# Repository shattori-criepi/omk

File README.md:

# OMK — おうちモニタキット

おうちモニタキット（OMK）は、一般財団法人電力中央研究所が開発した、住宅内の電力・環境・行動を計測するオープンなIoT基盤です。計測したい項目に合わせてセンサを組み合わせ、Raspberry Piをデータ収集・保存の中心となるGatewayとして使います。標準構成では、構築後は住宅側ネットワークに依存せず運用できます。

## できること

- 対応するセンサ・機器から、住宅の温度、湿度、空気質、電力、在不在などのデータを計測・収集できます。
- Raspberry Piに計測データを保存し、長期間の履歴として蓄積できます。
- Gateway内のローカルDashboardで、現在の計測値と機器の状態を確認できます。
- 保存済みデータをCSV/ZIPとしてUSBメモリへ書き出せます。
- SORACOM Harvestを利用する場合は、計測データをクラウドへ送信して保管できます。

## OMKの製作方法

初めて製作する方は、以下を上から順に読み、各ページ末尾の「次へ」で進めてください。GatewayとSEN66 Nodeを製作し、4-1のDashboardで計測確認まで完了します。

### 1. OMKの概要

- [1-1. OMK導入ガイド](docs/user/getting-started.md)
- [1-2. 対応センサ・機器と取得データ](docs/user/supported-devices.md)

### 2. OMK Gatewayを製作・セットアップする

- [2-1. OMKのパーツ構成](docs/user/parts-list.md)
- [2-2. Gatewayの組み立て](docs/user/gateway-assembly.md)
- [2-3. Gatewayセットアップ](docs/user/gateway-setup.md)

### 3. SEN66 Nodeを製作・セットアップする

- [3-1. SEN66 Nodeの組み立て](docs/user/sen66-node-assembly.md)
- [3-2. SEN66 Nodeをセットアップする](docs/user/esp32-node-setup.md)

### 4. Dashboardを使う

- [4-1. Dashboardの使い方](docs/user/dashboard.md)

ここまでで、推奨構成のOMKの製作・セットアップとSEN66による計測確認は完了です。

## 必要に応じて行う作業

製作完了後に、目的に合うページを選んでください。

- [BLEセンサを追加する](docs/user/ble-sensor-setup.md)
- [Bルートでスマートメーターを追加する](docs/user/broute-setup.md)
- [OMK Nodeで計測範囲を拡張する](docs/user/node-and-sensors.md)
- [中継専用OMK Nodeをセットアップする](docs/user/relay-node-setup.md)
- [Gatewayソフトウェアを更新・保守する](docs/user/gateway-maintenance.md)
- [OMK Nodeを更新・再設定する](docs/user/node-maintenance.md)
- [標準構成以外・高度な構成](docs/user/advanced-configuration.md)

## 参考情報

- [用語集](docs/user/glossary.md)
- [トラブルシューティング](docs/user/troubleshooting.md)

## 対応機器と取得データ

主な対応機器と取得データは次のとおりです。計測項目、接続方式、対応範囲の詳細は[「1-2. 対応センサ・機器と取得データ」](docs/user/supported-devices.md)を参照してください。

| 機器・センサ | 主な取得データ |
| --- | --- |
| 低圧スマートメーター（Bルート） | 系統の瞬時電力、買電・売電の積算電力量、30分ごとの買電量・売電量 |
| Sensirion SEN66 | 温度、相対湿度、CO₂濃度、粒子状物質、VOC Index、NOx Index |
| SwitchBot BLEセンサ | 温湿度、CO₂濃度、人感、開閉、プラグの消費電力・スイッチ状態、防水温湿度 |

## 動作確認環境と利用上の前提

OMKで動作確認している推奨構成は次のとおりです。

- Gateway：**Raspberry Pi 4、Raspberry Pi Touch Display 2（7インチ）、SORACOM Onyx**。OSは64ビットのRaspberry Pi OSを使用します。
- SEN66 Node：Sensirion SEN66とAtomS3 Lite。

初期セットアップには、既存Wi-Fiなどのインターネット接続を使います。APはAccess Point（アクセスポイント）の略です。OMK APを有効にすると、Raspberry Piの内蔵Wi-FiはOMK AP専用となり、外部Wi-Fiには接続できません。推奨構成ではSORACOM Onyxを外部通信と遠隔管理に使います。

標準構成以外の対応範囲と制約は、[「標準構成以外・高度な構成」](docs/user/advanced-configuration.md)を参照してください。

## OMKを開発する

このブランチは実機未検証のNative Mesh P1試験版です。[固定成果物・再現手順](experiments/native-mesh-p1-20261110/README.txt)と[移行資料](docs/developer/native-mesh-migration.md)を参照してください。既存公開用prebuiltは旧方式であり、今回の試験には使用しません。

- [アーキテクチャ](docs/developer/architecture.md)
- [開発ガイド](docs/developer/development.md)
- [Gatewayネットワーク設計](docs/developer/networking.md)
- [データ経路とMQTT仕様](docs/developer/data-and-mqtt.md)
- [リポジトリ構成](docs/developer/repository-structure.md)
- [設計判断の記録](docs/decisions/)

各サービスとファームウェアのREADMEには、個別の起動・設定・テスト・デバッグ方法を記載しています。

## 利用上の注意

OMKは研究・実験用途のシステムであり、商用製品やサービスではありません。計測値の正確性、完全性、継続性、対応機器との互換性、安定動作および安全性は保証しません。利用、改変、機器への接続、再配布は各利用者の判断と責任で行ってください。料金精算、契約上の計量、安全制御、保護制御など、高い信頼性を要する用途での利用は想定していません。

無保証および責任制限は[LICENSE](LICENSE)を参照してください。

## 成果発表

OMKを使用した技術開発等の成果を発表・報告する際は、可能な範囲でOMKを使用した旨の表示をお願いします。

## サポートと開発方針

GitHub等から利用する場合、機器の準備、構築、設定、運用、保守は利用者自身で行います。研究所および開発者は、個別環境への導入・設定支援、機器の製作代行、トラブル対応などの個別サポート、保守、動作保証を提供しません。

活用例、アイデア、改善案など、OMK全体に有用な情報の共有は歓迎します。ただし、相談や要望に対する回答、調査、機能追加、機器対応、修正などの対応は約束しません。

特定の利用者だけに必要な機能は、利用者自身のforkで開発・維持することを想定します。OMK全体に有用なアイデアは、研究目的、汎用性、保守性、開発優先度などを踏まえて採用を検討します。提案者にPR作成を求めるとは限らず、OMK開発側が実装する場合や、実装を見送る場合もあります。

GitHubでの情報共有・提案は、次の方針で受け付けます。

- GitHub Discussions：アイデア、活用例、利用方法の情報共有に使います。無償の個別サポート窓口ではありません。
- Issue：再現可能な不具合や、対応が決まった課題の管理に使います。単なる機能追加要望はDiscussionへ投稿してください。
- コード変更・機能追加の提案：まずDiscussionで目的、背景、想定用途、OMK全体への有用性を共有してください。OMKリポジトリへの取り込みを検討する場合は、必要に応じてIssue化やPR提出を案内します。PRの常時募集は行わず、事前相談のないPRへのレビュー、マージ、対応は約束しません。

電力中央研究所が主体となる研究・実証・被験者実験で設置する場合は、研究計画に基づき、研究実施側が設置、運用、保守、トラブル対応等を行います。上記の自己責任・サポート方針によって、実験協力者へ保守責任を転嫁することはありません。

## ライセンス

OMKのソフトウェアは[使用、複製および頒布に関する条件](LICENSE)で公開します。OMKの著作権は一般財団法人電力中央研究所に帰属します。

利用、改変、再配布、商用利用については、使用許諾条件に従ってください。

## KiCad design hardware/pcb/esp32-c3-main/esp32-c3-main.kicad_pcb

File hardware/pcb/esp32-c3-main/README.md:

# OMK ESP32-C3 MAIN Rev.A — CANCELLED reference design

> **Status: CANCELLED — NOT FOR FABRICATION**
>
> この一体型PCB計画は2026-08-04に正式中止された。回路図、PCB、footprint、生成スクリプトおよび監査資料は履歴・参考資料として保持するが、電気的・物理的に検証済みではなく、製造や発注に使用してはならない。後継構成は未決定である。決定記録は[ESP32-C3＋SEN66一体型PCB Rev.A 計画中止](../../../docs/decisions/esp32-c3-integrated-pcb-cancellation.md)を参照。

以下は中止時点のKiCad 9.0.8メイン基板回路図に関する履歴記録である。PCBレイアウト、BOM/CPL、Gerberは未完了であり、今後の作業計画を示すものではない。
回路図はA3横向き1枚に機能ブロックごとに整理し、右下のタイトルブロック領域を予約している。
メーカー型番、LCSC番号、Footprint、選定メモはシンボルプロパティとして保持するが、PDFには
Referenceと簡潔なValue以外を表示しない。ESP32-C3のアンテナkeepoutはPCB Phaseで確認する。
電源の現行仕様は AP63203WU-7 / C780769、C1=10uF、C2=100nF、C3=100nF BST–SW、
L1=4.7uH、C4/C5=22uF×2である。L1の電気的MPNはCoilcraft XGL4020-472MECへ選定済みで、
2D footprint `Inductor_SMD:L_Coilcraft_XxL4020` とMPN/LCSCはgenerator・正式回路図へ反映済みである。
3D/物理向き、JLC調達は未完了であり、C1/C4/C5のMLCC DCバイアスとともに製造リリースBLOCKERである。
詳細は [power-review.md](power-review.md) を正とする。R6/R7は4.7kΩ DNPで、キャリアR1/R2も同じDNP選択肢である。

## 再生成と検証

空テンプレート `esp32-c3-main.blank.kicad_sch` を
`kicad-sch-api==0.5.6` で読み込んで編集する。`.kicad_sch` を文字列置換していない。
生成前に標準ライブラリおよび公式Espressifシンボルのピン集合を検証し、すべての部品を0°で配置する。

```bash
KICAD_SYMBOL_DIR=/usr/share/kicad/symbols \
  .venv/bin/python scripts/generate_schematic.py
kicad-cli sch erc esp32-c3-main.kicad_sch --output erc-report.txt --severity-all
kicad-cli sch export pdf esp32-c3-main.kicad_sch \
  --output esp32-c3-main-schematic.pdf
```

生成中間物は `esp32-c3-main.generated.kicad_sch`。ERCにエラーがあれば、スクリプトは正式ファイルへ反映しない。
Git管理するEspressifシンボルは `symbols/Espressif.kicad_sym`、公式footprintは
`footprints/Espressif.pretty/` に同梱し、それぞれのプロジェクト表は
`sym-lib-table` / `fp-lib-table` に登録する。生成APIとの互換性のため、シンボルは公式リポジトリの
`legacy_kicad7`互換版である。

## 回路図ブロック

| ブロック | 実装内容 |
| --- | --- |
| USB-C | J1、VBUS PTC F1、CC1/CC2の5.1 kΩ Rd、USBLC6-2SC6 ESD、入力10 µF/100 nF、SBU NC、R3 0 Ω DNP shield option |
| 電源 | AP63203WU-7（3.3 V/2 A）、BST C3、4.7 µH L1、出力22 µF×2。L1はXGL4020-472MEC / C6012418と`Inductor_SMD:L_Coilcraft_XxL4020`をgenerator・正式回路図へ統合済み。3D・調達は未完了。 |
| MCU | ESP32-C3-MINI-1-H4X、3V3デカップリング、GPIO18/19 USB、GPIO6/7 I2C、GPIO9 BOOT、GPIO20/21 UART。NC/GND padを明示。 |
| BOOT/RESET | ENの10 kΩ pull-up、1 µF、RESETスイッチ、GPIO9の10 kΩ pull-up、BOOTスイッチ。 |
| I2C/外部 | 4.7 kΩ DNP pull-up、SEN66 1×4 J3、Qwiic JST SH J2、SDA/SCL TP。 |
| 評価用 | UART、+5V、+3V3、GND、USB、EN、BOOTのTPとGPIO3 status LED（DNP）。 |

## 主要部品

| Ref | MPN / 候補 | LCSC | Footprint | 状態 |
| --- | --- | --- | --- | --- |
| U1 | Espressif ESP32-C3-MINI-1-H4X | C41349510 | `Espressif:ESP32-C3-MINI-1` | 採用候補。JLC実装可否・在庫は発注時確認。 |
| U2 | Diodes AP63203WU-7 | C780769 | `Package_TO_SOT_SMD:TSOT-23-6` | 3.3 V/2 A buck候補。参照回路・在庫を最終照合。 |
| J1 | JAE DX07S016JA1R1500 | C3197885（候補、回路図propertyは未変更） | `Connector_USB:USB_C_Receptacle_JAE_DX07S016JA1R1500` | 中止前の評価はElectrical ACCEPT、JAE `SJ121837`のland/board-edge照合、3D/機構、調達はVERIFY。現行の製造リリース状態はCANCELLED。 |
| D1 | ST USBLC6-2SC6 | C7519 | `Package_TO_SOT_SMD:SOT-23-6` | USB ESD候補。 |
| J2 | JST SM04B-SRSS-TB(LF)(SN) | C160404 | `Connector_JST:JST_SH_SM04B-SRSS-TB_1x04-1MP_P1.00mm_Horizontal` | Qwiic。 |
| J3 | JST S4B-PH-K-S(LF)(SN) | C157926 | `Connector_JST:JST_PH_S4B-PH-K_1x04_P2.00mm_Horizontal` | キャリアJ2と同一変更セットで統合済み。物理向き/3D/mechanicalはPhase 3B VERIFY。 |
| L1 | Coilcraft XGL4020-472MEC | C6012418（発注時VERIFY） | `Inductor_SMD:L_Coilcraft_XxL4020`統合済み。旧`Inductor_SMD:L_Vishay_IHLP-2020`は不採用。 | Electrical/2D footprint ACCEPT・統合済み、3D/調達VERIFY、Release BLOCKER。 |

R3、R6/R7、R8/D2はDNP選択肢である。USB shieldのR3実装、I2C pull-up実装、LED実装は実機レビュー後に決定する。

## ERC

正式回路図のKiCad CLI ERCは **0 errors / 2 warnings**。警告はいずれもU1のプロジェクト内
Espressif symbol/footprint library設定に関するもので、J3統合による警告はない。全ピン番号は生成前検証済みである。
`kicad-sch-api`が現行KiCad 9/10形式の公式ライブラリを正しく埋め込めないため、公式KiCad 7互換版を使用したことに由来する。
意図的に残し、GUI目視確認時にU1の53ピンとfootprint対応を再照合する。`erc-report.txt`を参照。

## 中止時点の未完了確認事項（履歴）

以下は完了しておらず、計画中止により終了した項目である。後継設計で自動的に引き継がない。

- L1のJLC調達、3D/short-start lead向き確認、C1/C4/C5の公式DC-bias曲線、AP63203 EVMとのpin-by-pin照合を完了する。
- J1のJAE `SJ121837`、`JACS-30413`、`JAHL-30353-1`を取得し、land、shell/NPTH、board-edge datum、mating/rework clearanceを `usb-c-j1-footprint-audit.md` と照合する。J1、D1、J2、U1の現時点のJLC在庫・PCBA可否・CPL回転も確認する。
- U1のアンテナkeepout、露出GND pad/thermal via、USB差動対、buck SWノードをPCBレビューする。
- USB shieldの筐体/FG方針、J3の逆挿し対策、DNP部品の実装方針を承認する。
- J3/J2は裸2.54 mm案からJST `S4B-PH-K-S(LF)(SN)` / C157926へ双方同時変更済み。pin 1=3V3、2=GND、3=SDA、4=SCLを維持し、再生成/ERC/PDF確認済み。PCB上の回転・ハーネス外形・3D/mechanical確認はPhase 3Bで行う（詳細は `../jst-ph-header-selection.md`）。
- 回路図へ反映する変更順序とPhase 3Bゲートは [`../phase-3a-release-review.md`](../phase-3a-release-review.md) を正とする。
- 実機でUSB CDC、書込み、BOOT、SEN66、Wi-Fi/MQTT、電源リップルを評価する。

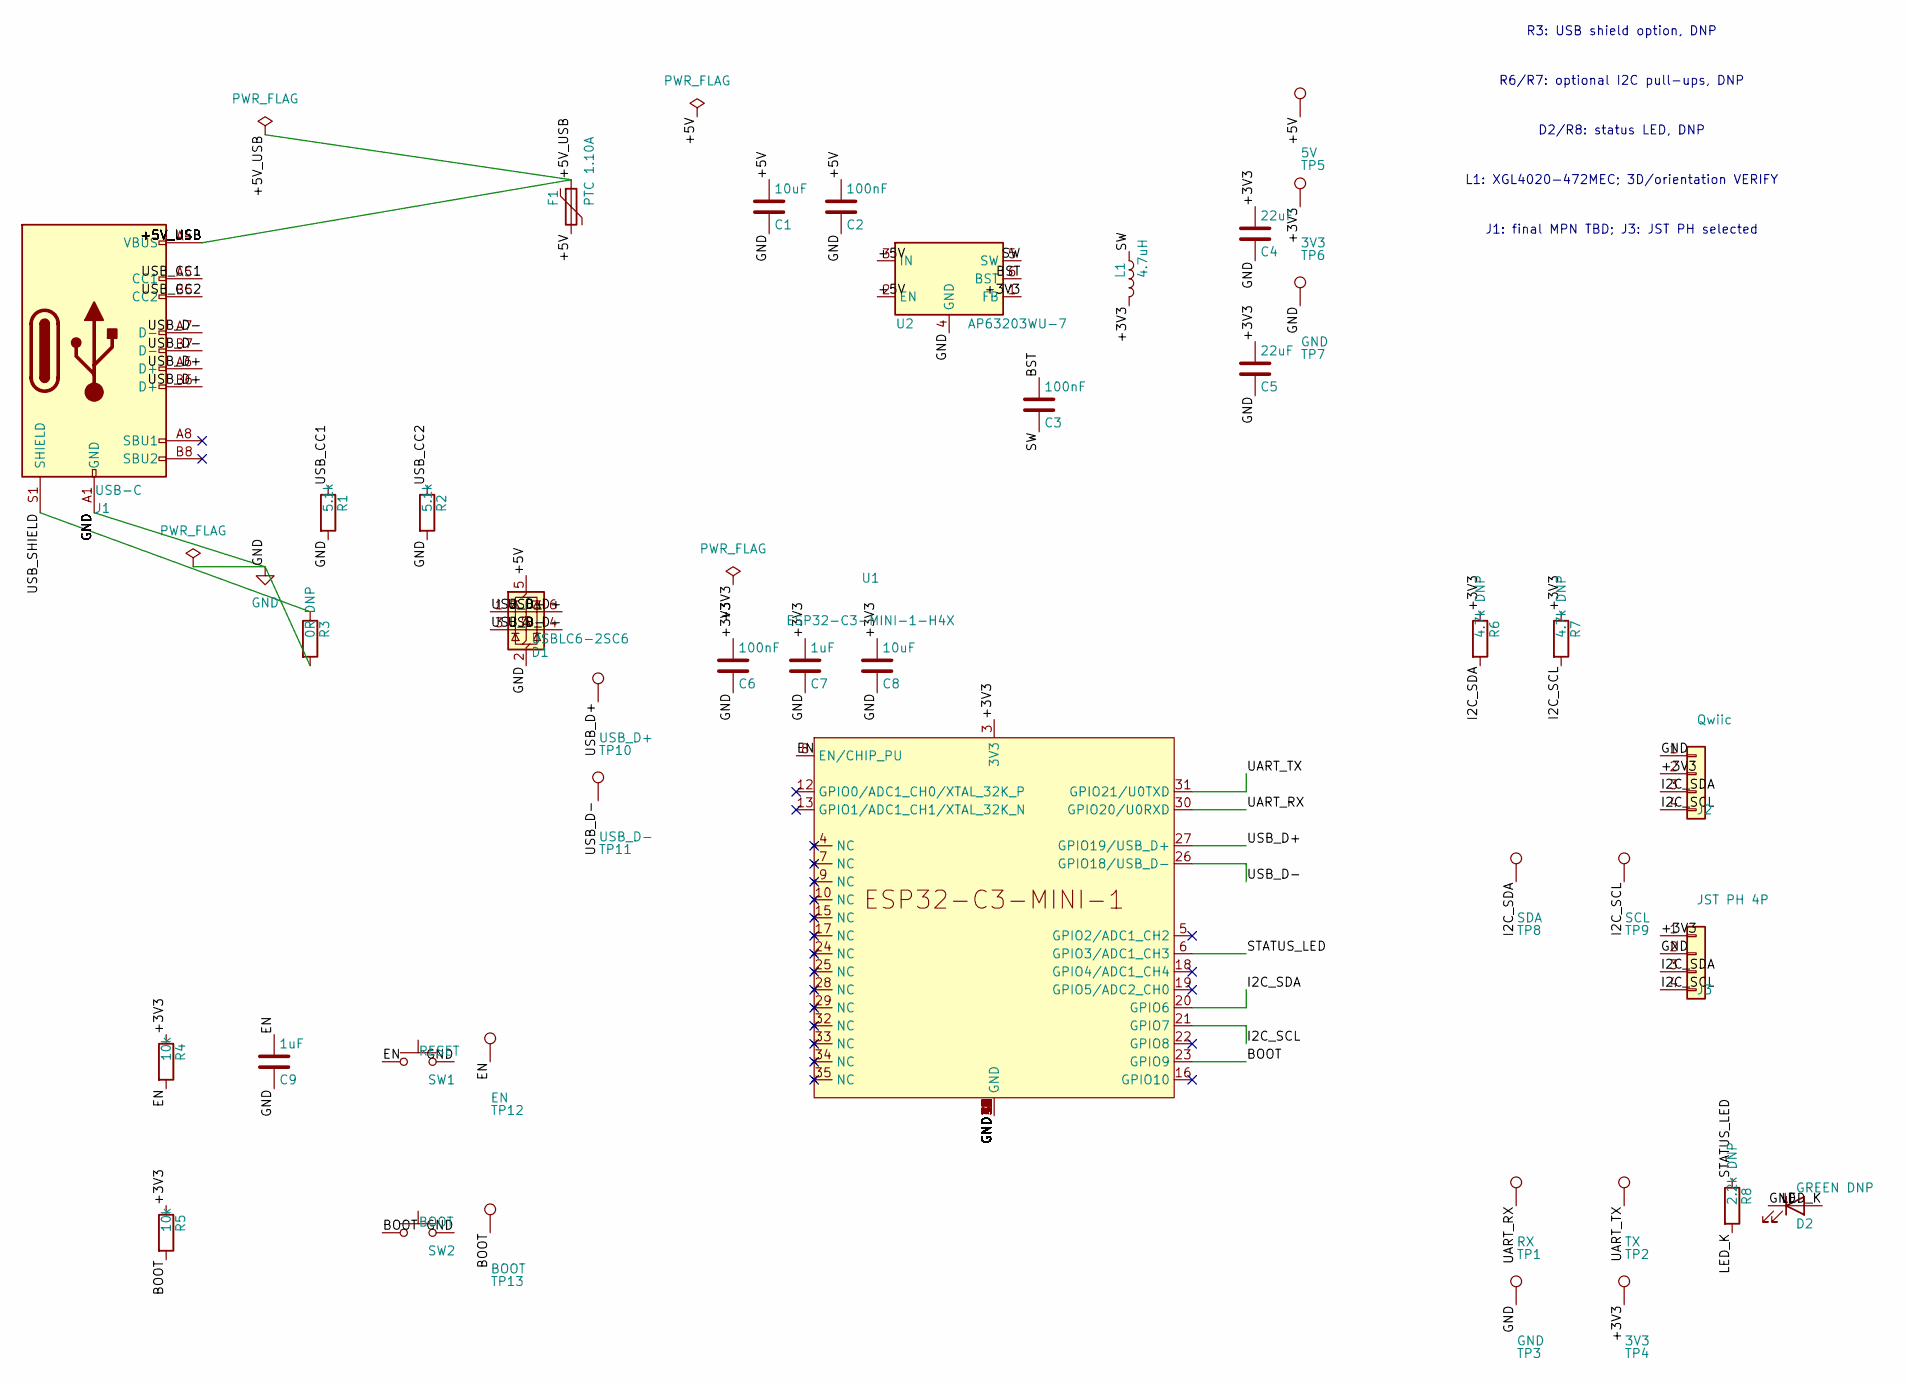
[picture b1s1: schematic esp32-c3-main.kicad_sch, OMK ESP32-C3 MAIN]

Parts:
C1, C8: 10uF; C_0805_2012Metric; Manufacturer Part Number Murata GRM21BR61A106KE19L
C2: 100nF; C_0402_1005Metric; Manufacturer Part Number Murata GRM155R71E104KE14D
C3, C6: 100nF; C_0402_1005Metric; Manufacturer Part Number Murata GRM155R71C104KA88D
C4, C5: 22uF; C_0805_2012Metric; Manufacturer Part Number Murata GRM21BR60J226ME39L
C7, C9: 1uF; C_0402_1005Metric; Manufacturer Part Number Murata GRM155R61A105KE15D
D1: USBLC6-2SC6; SOT-23-6; Manufacturer Part Number STMicroelectronics USBLC6-2SC6; LCSC C7519
D2: GREEN DNP; LED_0603_1608Metric; Manufacturer Part Number Kingbright APT1608LZGCK
F1: PTC 1.10A; Fuse_1812_4532Metric; Manufacturer Part Number Bourns MF-MSMF110-2
J1: USB-C; USB_C_Receptacle_JAE_DX07S016JA1R1500; Manufacturer Part Number JAE DX07S016JA1R1500; LCSC TBD
J2: Qwiic; JST_SH_SM04B-SRSS-TB_1x04-1MP_P1.00mm_Horizontal; Manufacturer Part Number JST SM04B-SRSS-TB(LF)(SN); LCSC C160404
J3: JST PH 4P; JST_PH_S4B-PH-K_1x04_P2.00mm_Horizontal; Manufacturer Part Number S4B-PH-K-S(LF)(SN); LCSC C157926
L1: 4.7uH; L_Coilcraft_XxL4020; Manufacturer Part Number XGL4020-472MEC; LCSC C6012418
R1, R2: 5.1k; R_0402_1005Metric; Manufacturer Part Number Yageo RC0402FR-075K1L
R3: 0R DNP; R_0402_1005Metric; Manufacturer Part Number Yageo RC0402JR-070RL
R4, R5: 10k; R_0402_1005Metric; Manufacturer Part Number Yageo RC0402FR-0710KL
R6, R7: 4.7k DNP; R_0402_1005Metric; Manufacturer Part Number Yageo RC0402FR-074K7L
R8: 2.2k DNP; R_0402_1005Metric; Manufacturer Part Number Yageo RC0402FR-072K2L
SW1: RESET; SW_SPST_B3U-1000P; Manufacturer Part Number Omron B3U-1000P
SW2: BOOT; SW_SPST_B3U-1000P; Manufacturer Part Number Omron B3U-1000P
TP1: RX; TestPoint_Pad_D2.0mm; Manufacturer Part Number Keystone 5015
TP2: TX; TestPoint_Pad_D2.0mm; Manufacturer Part Number Keystone 5015
TP3, TP7: GND; TestPoint_Pad_D2.0mm; Manufacturer Part Number Keystone 5015
TP4, TP6: 3V3; TestPoint_Pad_D2.0mm; Manufacturer Part Number Keystone 5015
TP5: 5V; TestPoint_Pad_D2.0mm; Manufacturer Part Number Keystone 5015
TP8: SDA; TestPoint_Pad_D2.0mm; Manufacturer Part Number Keystone 5015
TP9: SCL; TestPoint_Pad_D2.0mm; Manufacturer Part Number Keystone 5015
TP10: USB_D+; TestPoint_Pad_D2.0mm; Manufacturer Part Number Keystone 5015
TP11: USB_D-; TestPoint_Pad_D2.0mm; Manufacturer Part Number Keystone 5015
TP12: EN; TestPoint_Pad_D2.0mm; Manufacturer Part Number Keystone 5015
TP13: BOOT; TestPoint_Pad_D2.0mm; Manufacturer Part Number Keystone 5015
U1: ESP32-C3-MINI-1-H4X; ESP32-C3-MINI-1; Manufacturer Part Number Espressif ESP32-C3-MINI-1-H4X; LCSC C41349510
U2: AP63203WU-7; TSOT-23-6; Manufacturer Part Number Diodes Inc. AP63203WU-7; LCSC C780769

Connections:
/+3V3: C4.1, C5.1, C6.1, C7.1, C8.1, J2.2, J3.1, L1.2, R4.1, R5.1, R6.1, R7.1, TP4.1, TP6.1, U1.3 (3V3), U2.1 (FB)
/+5V: C1.1, C2.1, D1.5 (VBUS), F1.2, TP5.1, U2.2 (EN), U2.3 (IN)
/+5V_USB: F1.1, J1.A4 (VBUS), J1.A9 (VBUS), J1.B4 (VBUS), J1.B9 (VBUS)
/BOOT: R5.2, SW2.1, TP13.1, U1.23 (GPIO9)
/BST: C3.1, U2.6 (BST)
/EN: C9.1, R4.2, SW1.1, TP12.1, U1.8 (EN/CHIP_PU)
/I2C_SCL: J2.4, J3.4, R7.2, TP9.1, U1.21 (GPIO7)
/I2C_SDA: J2.3, J3.3, R6.2, TP8.1, U1.20 (GPIO6)
/LED_K: D2.2 (A), R8.2
/STATUS_LED: R8.1, U1.6 (GPIO3/ADC1_CH3)
/SW: C3.2, L1.1, U2.5 (SW)
/UART_RX: TP1.1, U1.30 (GPIO20/U0RXD)
/UART_TX: TP2.1, U1.31 (GPIO21/U0TXD)
/USB_CC1: J1.A5 (CC1), R1.1
/USB_CC2: J1.B5 (CC2), R2.1
/USB_D+: D1.1 (I/O1), D1.6 (I/O1), J1.A6 (D+), J1.B6 (D+), TP10.1, U1.27 (GPIO19/USB_D+)
/USB_D-: D1.3 (I/O2), D1.4 (I/O2), J1.A7 (D-), J1.B7 (D-), TP11.1, U1.26 (GPIO18/USB_D-)
/USB_SHIELD: J1.S1 (SHIELD), R3.1
GND: C1.2, C2.2, C4.2, C5.2, C6.2, C7.2, C8.2, C9.2, D1.2 (GND), D2.1 (K), J1.A1 (GND), J1.A12 (GND), J1.B1 (GND), J1.B12 (GND), J2.1, J3.2, R1.2, R2.2, R3.2, SW1.2, SW2.2, TP3.1, TP7.1, U1.1 (GND), U1.2 (GND), U1.11 (GND), U1.14 (GND), U1.36 (GND), U1.37 (GND), U1.38 (GND), U1.39 (GND), U1.40 (GND), U1.41 (GND), U1.42 (GND), U1.43 (GND), U1.44 (GND), U1.45 (GND), U1.46 (GND), U1.47 (GND), U1.48 (GND), U1.49 (GND), U1.50 (GND), U1.51 (GND), U1.52 (GND), U1.53 (GND), U2.4 (GND)

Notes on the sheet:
R3: USB shield option, DNP
R6/R7: optional I2C pull-ups, DNP
D2/R8: status LED, DNP
L1: XGL4020-472MEC; 3D/orientation VERIFY
J1: final MPN TBD; J3: JST PH selected

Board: 2 copper layers, 41 parts (0 on the bottom side), 19 nets, no tracks yet.
